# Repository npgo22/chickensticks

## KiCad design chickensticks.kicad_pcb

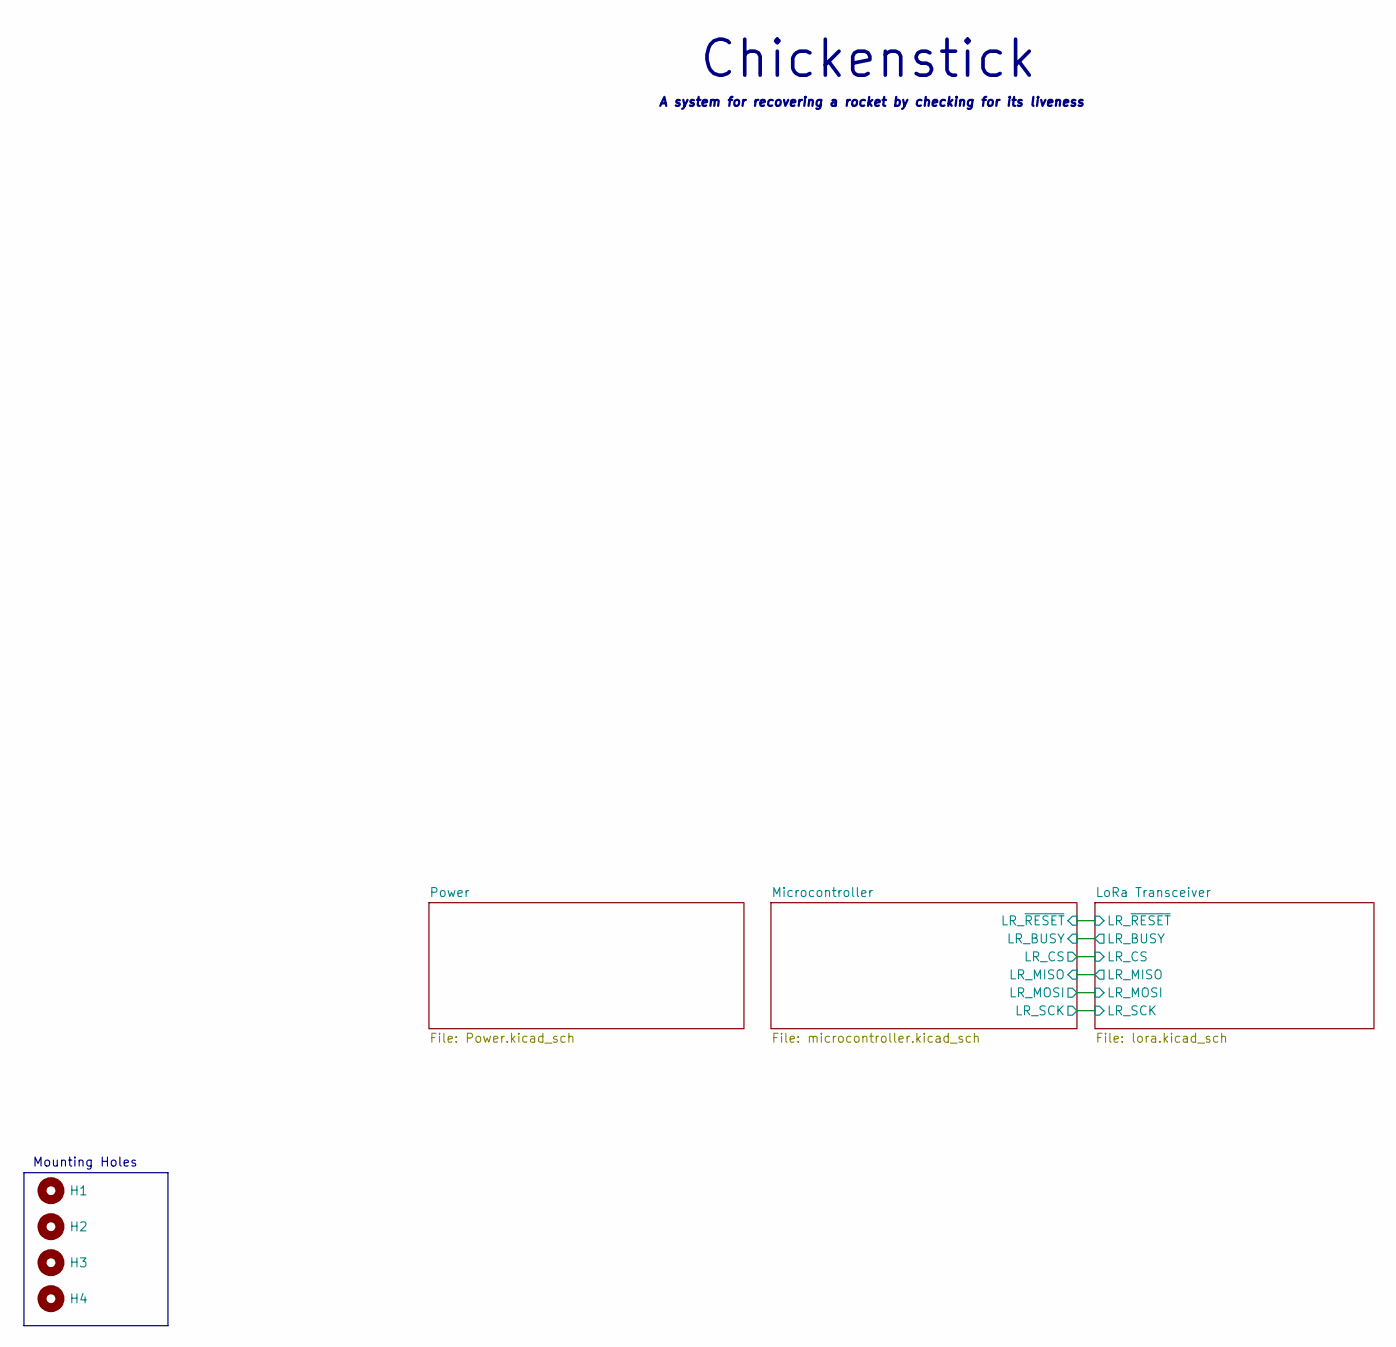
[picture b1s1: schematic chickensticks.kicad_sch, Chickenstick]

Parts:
H1, H2, H3, H4: MountingHole; MountingHole_3.2mm_M3

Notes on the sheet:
Chickenstick
A system for recovering a rocket by checking for its liveness
Mounting Holes

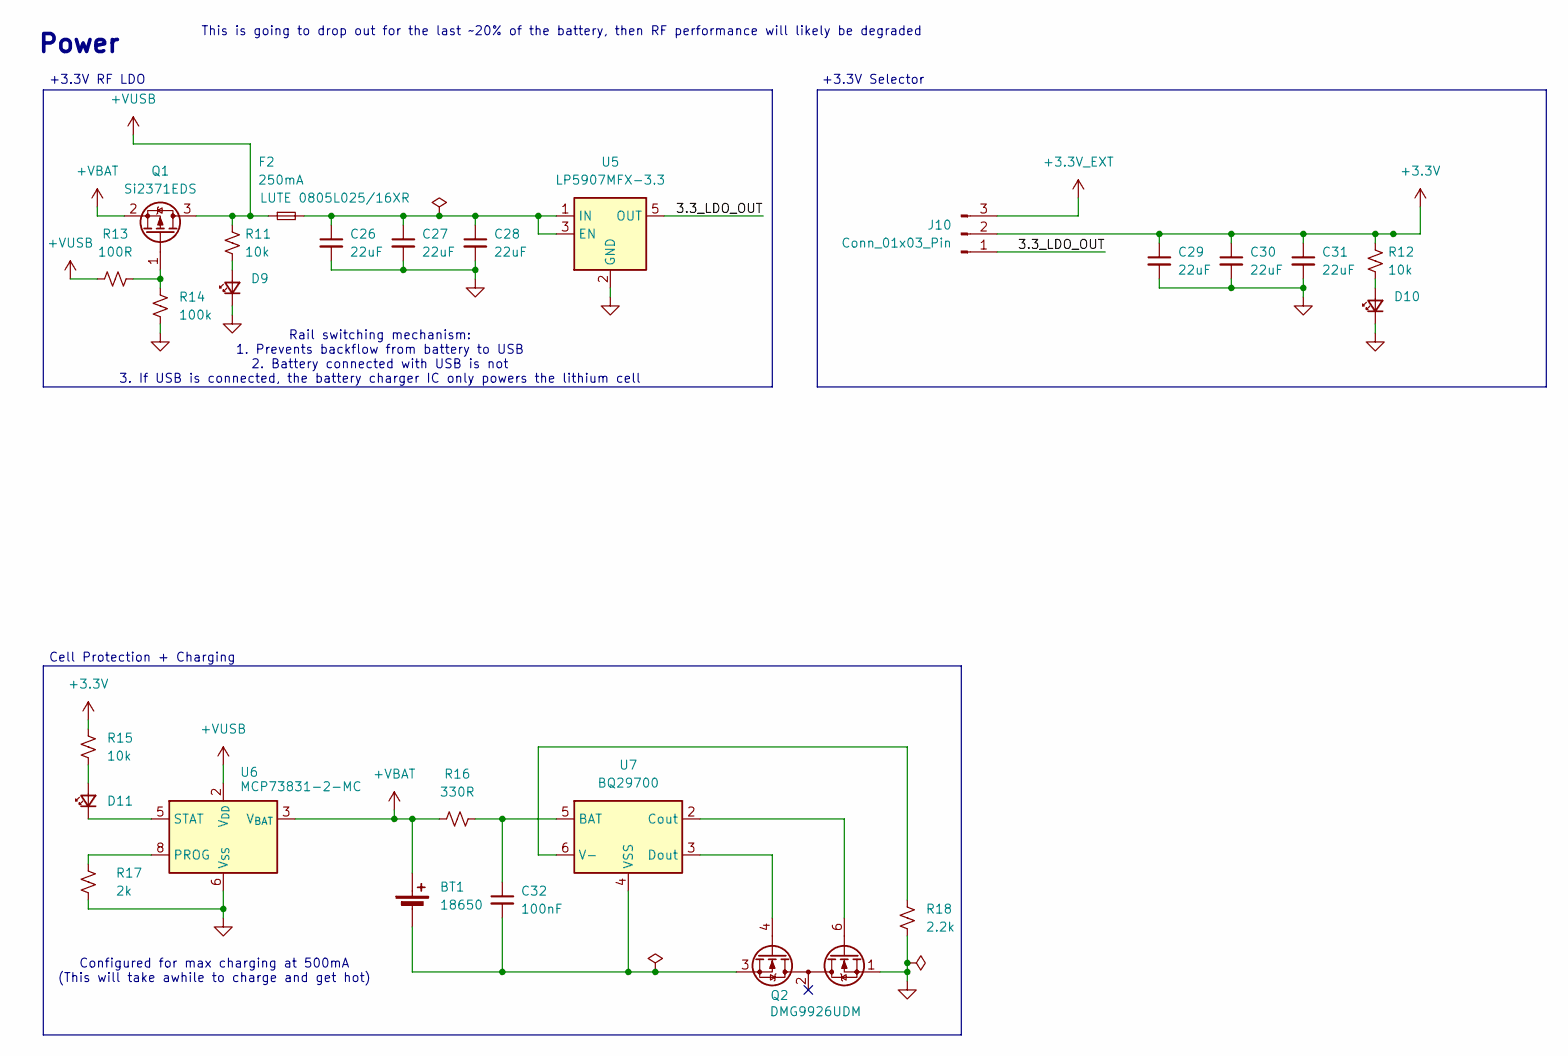
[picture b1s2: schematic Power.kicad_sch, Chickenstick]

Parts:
BT1: 18650; BatteryHolder_Keystone_1042_1x18650
C26, C27, C28, C29, C30, C31: 22uF; C_0805
C32: 100nF; C_0603
D9, D10, D11: LED_Small; LED_0603
F2: 250mA; Fuse_0805_2012Metric
J10: Conn_01x03_Pin; PinHeader_1x03_P2.54mm_Vertical
Q1: Si2371EDS; SOT-23
Q2: DMG9926UDM; SOT-23-6
R11, R12, R15: 10k; R_0603
R13: 100R; R_0603
R14: 100k; R_0603
R16: 330R; R_0603
R17: 2k; R_0603
R18: 2.2k; R_0603
U5: LP5907MFX-3.3; SOT-23-5
U6: MCP73831-2-MC; DFN-8-1EP_3x2mm_P0.5mm_EP1.7x1.4mm
U7: BQ29700; WSON-6_1.5x1.5mm_P0.5mm

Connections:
+3.3V: C29.1, C30.1, C31.1, J10.2, R12.1, R15.2; also elsewhere on the board
+3.3V_EXT: J10.3; also elsewhere on the board
+VUSB: F2.1, Q1.3 (D), R11.1, R13.1, U6.1 (V_{DD}), U6.2 (V_{DD}); also elsewhere on the board
/Power/3.3_LDO_OUT: J10.1, U5.5 (OUT)
unnamed: BT1.2 (-), C32.2, Q2.3 (S2), U7.4 (VSS)
unnamed: D9.2 (A), R11.2
unnamed: D10.2 (A), R12.2
unnamed: D11.2 (A), R15.1
unnamed: D11.1 (K), U6.5 (STAT)
unnamed: Q1.1 (G), R13.2, R14.1
unnamed: Q2.6 (G1), U7.2 (Cout)
unnamed: Q2.4 (G2), U7.3 (Dout)
unnamed: C26.1, C27.1, C28.1, F2.2, U5.1 (IN), U5.3 (EN)
unnamed: R17.1, U6.8 (PROG)
unnamed: C32.1, R16.2, U7.5 (BAT)
unnamed: R18.1, U7.6 (V-)

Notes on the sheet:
Configured for max charging at 500mA (This will take awhile to charge and get hot)
This is going to drop out for the last ~20% of the battery, then RF performance will likely be degraded
Power
Rail switching mechanism: 1. Prevents backflow from battery to USB 2. Battery connected with USB is not 3. If USB is connected, the battery charger IC only powers the lithium cell
+3.3V RF LDO
Cell Protection + Charging
+3.3V Selector

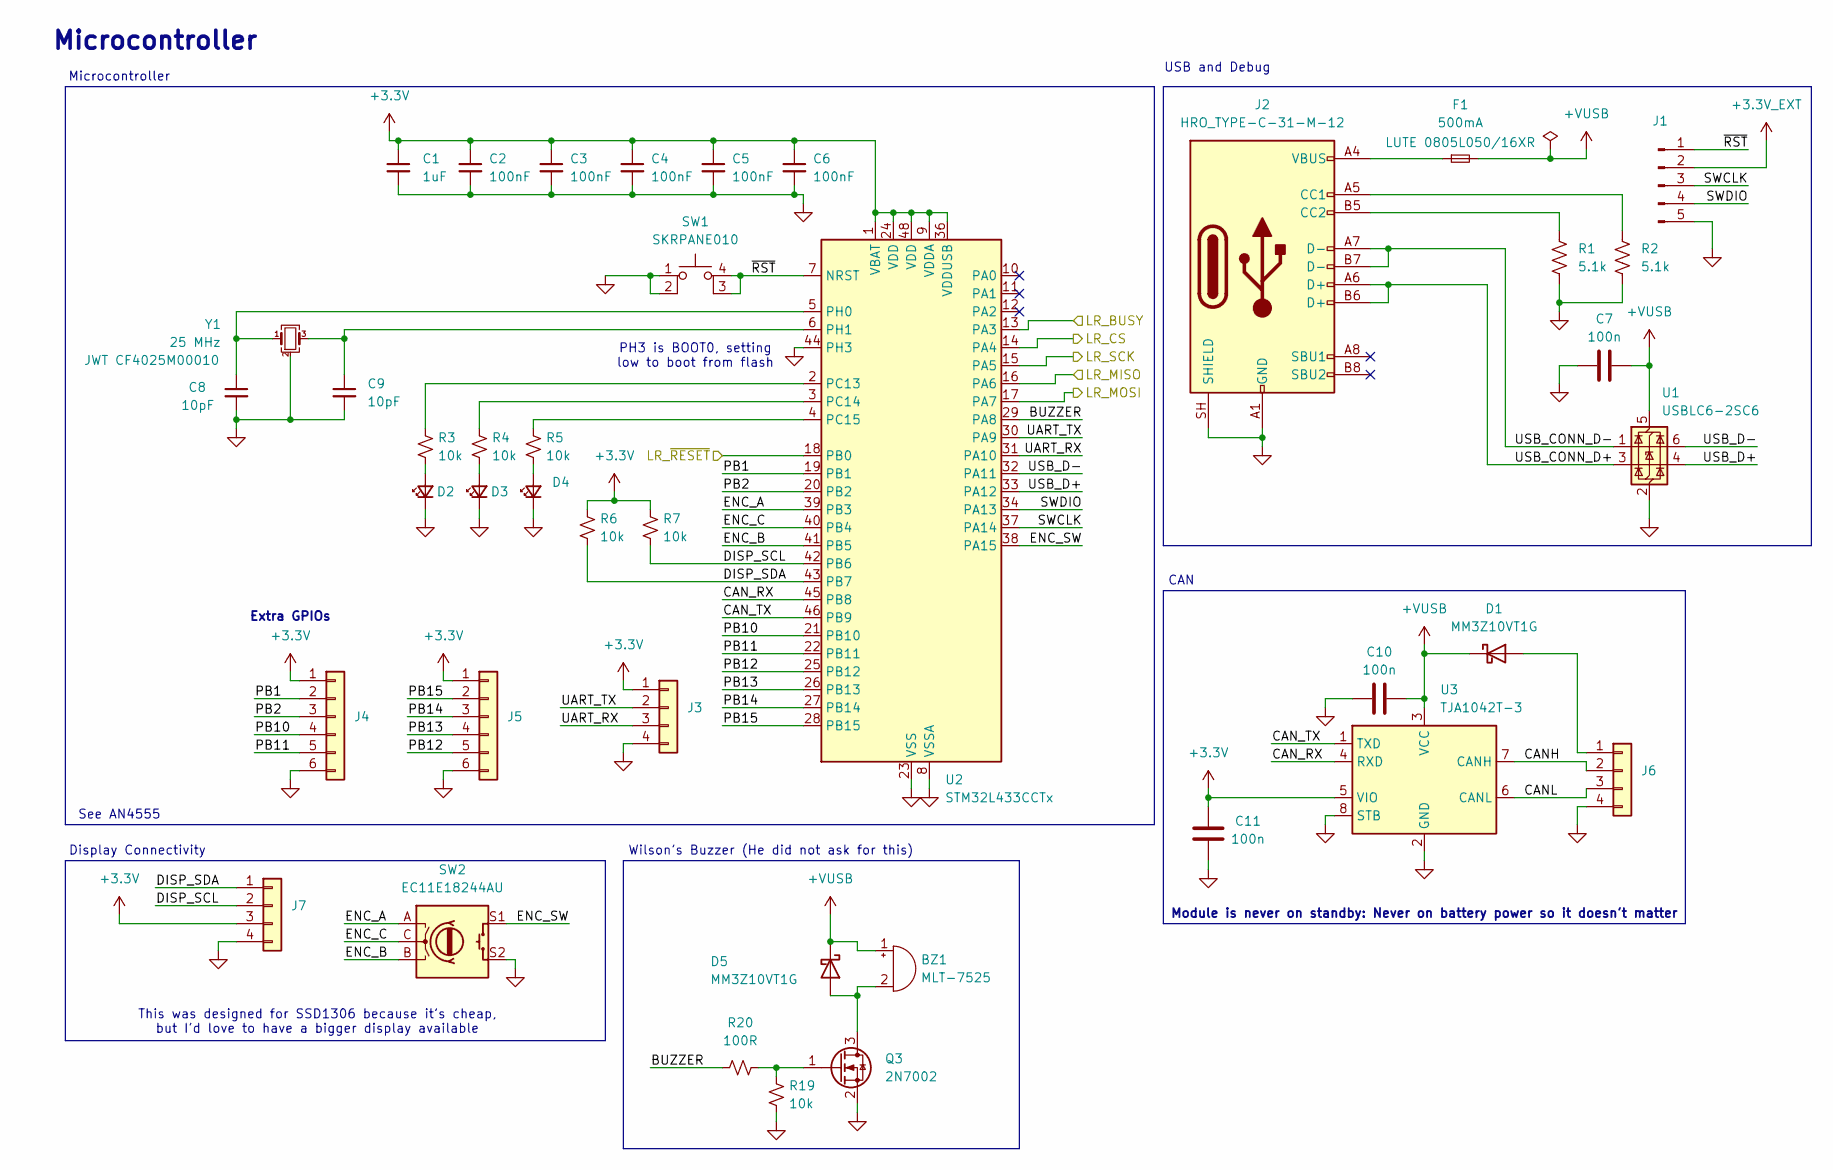
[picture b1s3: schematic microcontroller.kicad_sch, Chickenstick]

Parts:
BZ1: MLT-7525
C1: 1uF; C_0805
C2, C3, C4, C5, C6: 100nF; C_0603
C7, C10, C11: 100n; C_0603
C8, C9: 10pF; C_0603
D1, D5: MM3Z10VT1G; SOD-323
D2, D3, D4: LED_Small; LED_0603
F1: 500mA; Fuse_0805_2012Metric
J1: Conn_01x05_Pin; PinHeader_1x05_P2.54mm_Vertical
J2: HRO_TYPE-C-31-M-12; USB_C_Receptacle_HRO_TYPE-C-31-M-12
J3, J6, J7: Conn_01x04; PinHeader_1x04_P2.54mm_Vertical
J4, J5: Conn_01x06; PinHeader_1x06_P2.54mm_Vertical
Q3: 2N7002; SOT-23
R1, R2: 5.1k; R_0603
R3, R4, R5, R6, R7, R19: 10k; R_0603
R20: 100R; R_0603
SW1: SKRPANE010
SW2: EC11E18244AU; RotaryEncoder_Alps_EC11E-Switch_Vertical_H20mm_MountingHoles
U1: USBLC6-2SC6; SOT-23-6
U2: STM32L433CCTx; LQFP-48_7x7mm_P0.5mm
U3: TJA1042T-3; SOIC-8_3.9x4.9mm_P1.27mm
Y1: 25 MHz; 3225-4P-L

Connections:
+3.3V: C1.1, C2.1, C3.1, C4.1, C5.1, C6.1, C11.2, J3.1, J4.1, J5.1, J7.3, R6.1, R7.1, U2.1 (VBAT), U2.9 (VDDA), U2.24 (VDD), U2.36 (VDDUSB), U2.48 (VDD), U3.5 (VIO); also elsewhere on the board
+3.3V_EXT: J1.2; also elsewhere on the board
+VUSB: BZ1.1 (+), C7.2, C10.2, D1.1 (K), D5.1 (K), F1.2, U1.5 (VBUS), U3.3 (VCC); also elsewhere on the board
/LoRa Transceiver/LR_BUSY: U2.13 (PA3); also elsewhere on the board
/LoRa Transceiver/LR_CS: U2.14 (PA4); also elsewhere on the board
/LoRa Transceiver/LR_MISO: U2.16 (PA6); also elsewhere on the board
/LoRa Transceiver/LR_MOSI: U2.17 (PA7); also elsewhere on the board
/LoRa Transceiver/LR_SCK: U2.15 (PA5); also elsewhere on the board
/LoRa Transceiver/LR_~RESET: U2.18 (PB0); also elsewhere on the board
/Microcontroller/BUZZER: R20.1, U2.29 (PA8)
/Microcontroller/CANH: J6.2, U3.7 (CANH)
/Microcontroller/CANL: J6.3, U3.6 (CANL)
/Microcontroller/CAN_RX: U2.45 (PB8), U3.4 (RXD)
/Microcontroller/CAN_TX: U2.46 (PB9), U3.1 (TXD)
/Microcontroller/DISP_SCL: J7.2, R7.2, U2.42 (PB6)
/Microcontroller/DISP_SDA: J7.1, R6.2, U2.43 (PB7)
/Microcontroller/ENC_A: SW2.A, U2.39 (PB3)
/Microcontroller/ENC_B: SW2.B, U2.41 (PB5)
/Microcontroller/ENC_C: SW2.C, U2.40 (PB4)
/Microcontroller/ENC_SW: SW2.S1, U2.38 (PA15)
/Microcontroller/PB1: J4.2, U2.19 (PB1)
/Microcontroller/PB2: J4.3, U2.20 (PB2)
/Microcontroller/PB10: J4.4, U2.21 (PB10)
/Microcontroller/PB11: J4.5, U2.22 (PB11)
/Microcontroller/PB12: J5.5, U2.25 (PB12)
/Microcontroller/PB13: J5.4, U2.26 (PB13)
/Microcontroller/PB14: J5.3, U2.27 (PB14)
/Microcontroller/PB15: J5.2, U2.28 (PB15)
/Microcontroller/SWCLK: J1.3, U2.37 (PA14)
/Microcontroller/SWDIO: J1.4, U2.34 (PA13)
/Microcontroller/UART_RX: J3.3, U2.31 (PA10)
/Microcontroller/UART_TX: J3.2, U2.30 (PA9)
/Microcontroller/USB_CONN_D+: J2.A6 (D+), J2.B6 (D+), U1.3 (I/O2)
/Microcontroller/USB_CONN_D-: J2.A7 (D-), J2.B7 (D-), U1.1 (I/O1)
/Microcontroller/USB_D+: U1.4 (I/O2), U2.33 (PA12)
/Microcontroller/USB_D-: U1.6 (I/O1), U2.32 (PA11)
/Microcontroller/~RST: J1.1, SW1.3 (K), SW1.4 (A), U2.7 (NRST)
unnamed: BZ1.2 (-), D5.2 (A), Q3.3 (D)
unnamed: D1.2 (A), J6.1
unnamed: D2.2 (A), R3.2
unnamed: D3.2 (A), R4.2
unnamed: D4.2 (A), R5.2
unnamed: F1.1, J2.A4 (VBUS), J2.A9 (VBUS), J2.B4 (VBUS), J2.B9 (VBUS)
unnamed: J2.A5 (CC1), R2.1
unnamed: J2.B5 (CC2), R1.1
unnamed: Q3.1 (G), R19.1, R20.2
unnamed: R3.1, U2.2 (PC13)
unnamed: R4.1, U2.3 (PC14)
unnamed: R5.1, U2.4 (PC15)
unnamed: C8.1, U2.5 (PH0), Y1.1
unnamed: C9.1, U2.6 (PH1), Y1.3

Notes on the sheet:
Microcontroller
Extra GPIOs
Module is never on standby: Never on battery power so it doesn't matter
See AN4555
Display Connectivity
Wilson's Buzzer (He did not ask for this)
This was designed for SSD1306 because it's cheap, but I'd love to have a bigger display available
CAN
PH3 is BOOT0, setting low to boot from flash
USB and Debug

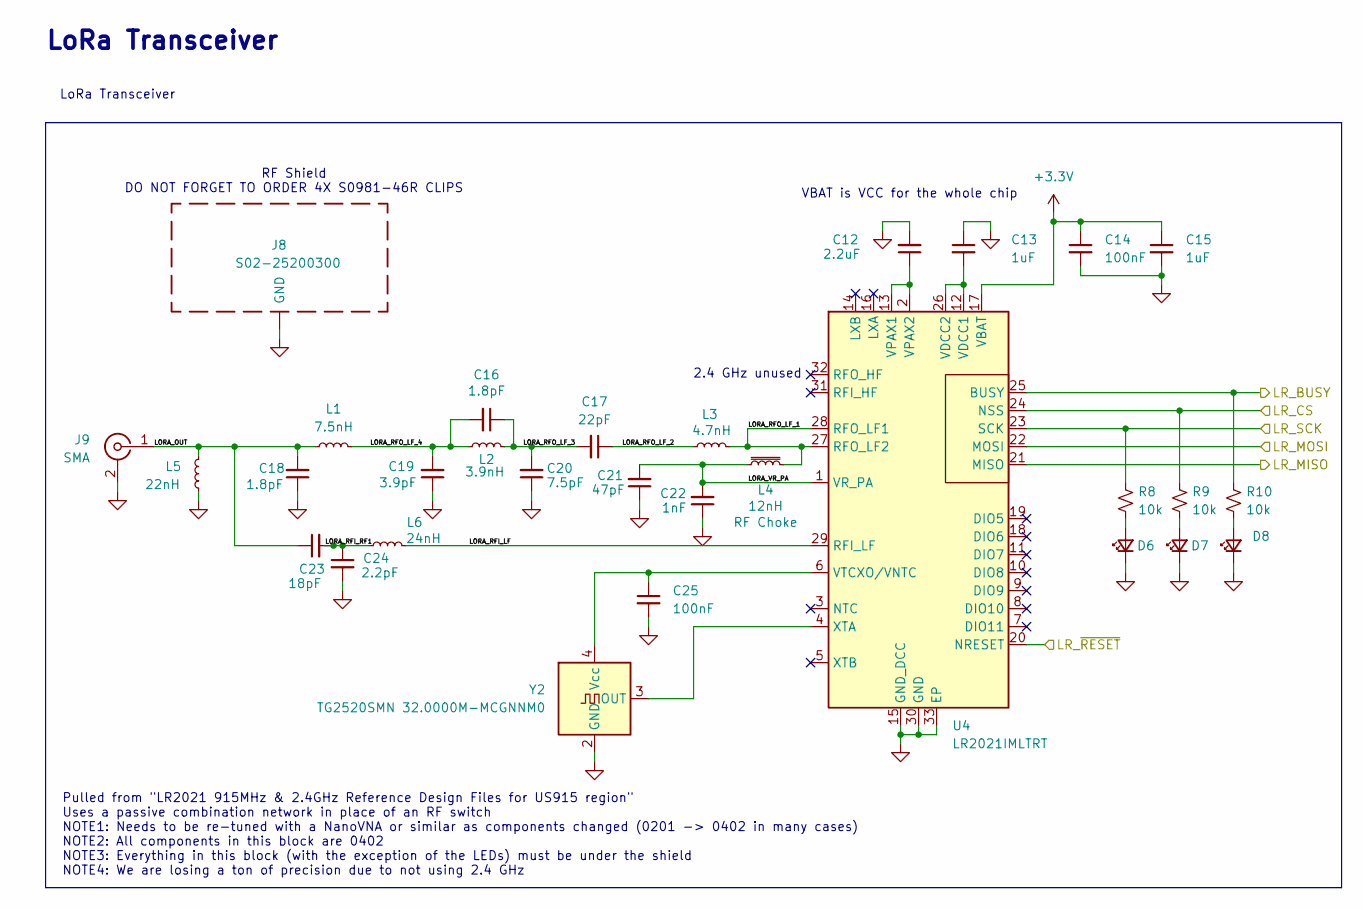
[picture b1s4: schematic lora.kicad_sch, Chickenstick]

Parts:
C12: 2.2uF; C_0805
C13, C15: 1uF; C_0805
C14, C25: 100nF; C_0603
C16, C18: 1.8pF; C_0402
C17: 22pF; C_0402
C19: 3.9pF; C_0402
C20: 7.5pF; C_0402
C21: 47pF; C_0402
C22: 1nF; C_0402
C23: 18pF; C_0402
C24: 2.2pF; C_0402
D6, D7, D8: LED_Small; LED_0603
J8: S02-25200300; S02-25200300-Outline
J9: SMA; SMA_Amphenol_132203-12_Horizontal
L1: 7.5nH; L_0402
L2: 3.9nH; L_0402
L3: 4.7nH; L_0402
L4: 12nH; L_0402
L5: 22nH; L_0402
L6: 24nH; L_0402
R8, R9, R10: 10k; R_0603
U4: LR2021IMLTRT; QFN-32_EP_5.8x5.8_Pitch0.5mm
Y2: TG2520SMN 32.0000M-MCGNNM0; Oscillator_SMD_SeikoEpson_TG2520SMN-xxx-xxxxxx-4Pin_2.5x2.0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

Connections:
+3.3V: C14.1, C15.1, U4.17 (VBAT); also elsewhere on the board
/LoRa Transceiver/LORA_OUT: C18.2, C23.1, J9.1 (In), L1.1, L5.2
/LoRa Transceiver/LORA_RFI_LF: L6.2, U4.29 (RFI_LF)
/LoRa Transceiver/LORA_RFI_RF1: C23.2, C24.1, L6.1
/LoRa Transceiver/LORA_RFO_LF_1: L3.2, L4.2, U4.27 (RFO_LF2), U4.28 (RFO_LF1)
/LoRa Transceiver/LORA_RFO_LF_2: C17.1, L3.1
/LoRa Transceiver/LORA_RFO_LF_3: C16.1, C17.2, C20.2, L2.2
/LoRa Transceiver/LORA_RFO_LF_4: C16.2, C19.2, L1.2, L2.1
/LoRa Transceiver/LORA_VR_PA: C21.2, C22.2, L4.1, U4.1 (VR_PA)
/LoRa Transceiver/LR_BUSY: R10.1, U4.25 (BUSY); also elsewhere on the board
/LoRa Transceiver/LR_CS: R9.1, U4.24 (NSS); also elsewhere on the board
/LoRa Transceiver/LR_MISO: U4.21 (MISO); also elsewhere on the board
/LoRa Transceiver/LR_MOSI: U4.22 (MOSI); also elsewhere on the board
/LoRa Transceiver/LR_SCK: R8.1, U4.23 (SCK); also elsewhere on the board
/LoRa Transceiver/LR_~RESET: U4.20 (NRESET); also elsewhere on the board
unnamed: D6.2 (A), R8.2
unnamed: D7.2 (A), R9.2
unnamed: D8.2 (A), R10.2
unnamed: C13.2, U4.12 (VDCC1), U4.26 (VDCC2)
unnamed: C12.1, U4.2 (VPAX2), U4.13 (VPAX1)
unnamed: C25.1, U4.6 (VTCXO/VNTC), Y2.4 (Vcc)
unnamed: U4.4 (XTA), Y2.3 (OUT)

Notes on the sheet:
RF Shield DO NOT FORGET TO ORDER 4X S0981-46R CLIPS
2.4 GHz unused
Pulled from "LR2021 915MHz & 2.4GHz Reference Design Files for US915 region" Uses a passive combination network in place of an RF switch NOTE1: Needs to be re-tuned with a NanoVNA or similar as components changed (0201 -> 0402 in many cases) NOTE2: All components in this block are 0402 NOTE3: Every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
VBAT is VCC for the whole chip
LoRa Transceiver

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
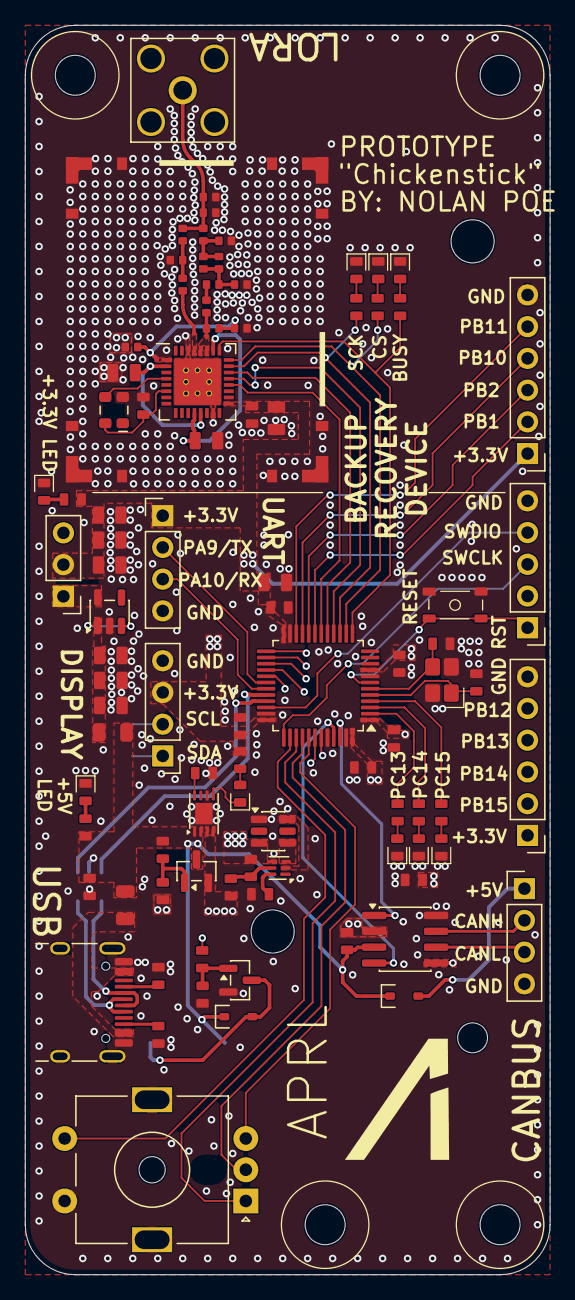
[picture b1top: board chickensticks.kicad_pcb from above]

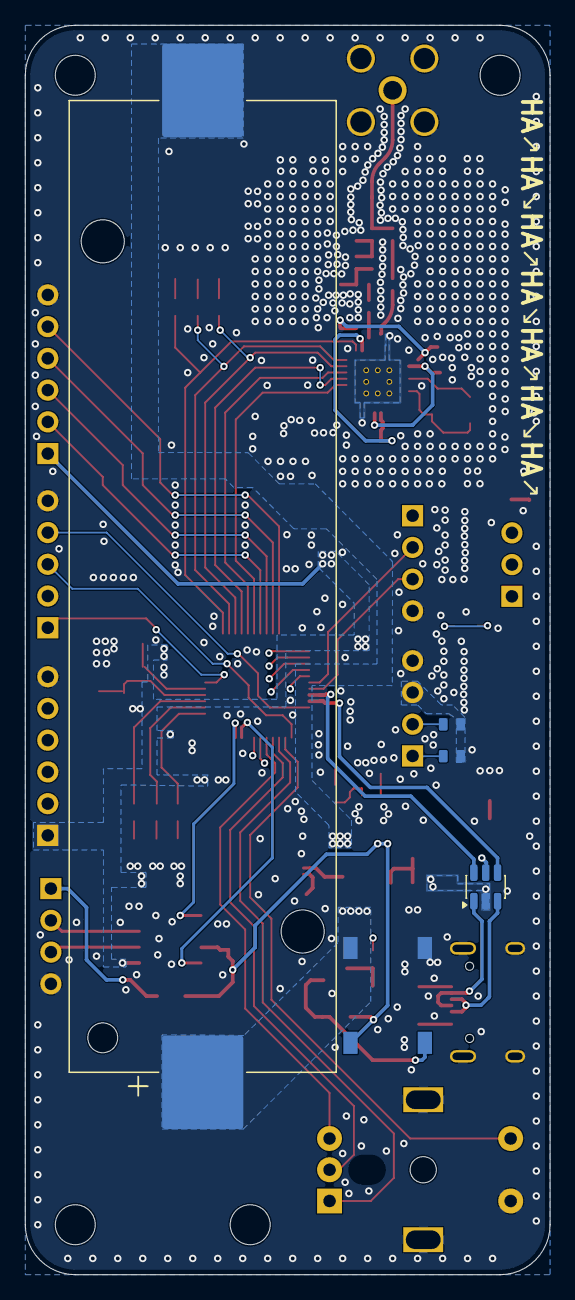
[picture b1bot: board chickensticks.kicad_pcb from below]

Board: 4 copper layers, 42.0 x 100.0 mm, 101 parts (5 on the bottom side), 81 nets.

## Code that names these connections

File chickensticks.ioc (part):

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Mcu.Name=STM32L433C(B-C)Tx
Mcu.Package=LQFP48
Mcu.UserName=STM32L433CCTx
PA10.Mode=Asynchronous
PA10.Signal=USART1_RX
PA11.Mode=Device
PA11.Signal=USB_DM
PA12.Mode=Device
PA12.Signal=USB_DP
PA13\ (JTMS-SWDIO).Mode=Serial_Wire
PA13\ (JTMS-SWDIO).Signal=SYS_JTMS-SWDIO
PA14\ (JTCK-SWCLK).Mode=Serial_Wire
PA14\ (JTCK-SWCLK).Signal=SYS_JTCK-SWCLK
PA15\ (JTDI).Signal=GPIO_Input
PA3.GPIOParameters=GPIO_Label
PA3.GPIO_Label=LR_BUSY
PA3.Signal=GPIO_Input
PA4.GPIOParameters=GPIO_Label
PA4.GPIO_Label=LR_CS
PA4.Signal=GPIO_Output
PA5.Mode=Full_Duplex_Master
PA5.Signal=SPI1_SCK
PA6.Mode=Full_Duplex_Master
PA6.Signal=SPI1_MISO
PA7.Mode=Full_Duplex_Master
PA7.Signal=SPI1_MOSI
PA9.Mode=Asynchronous
PA9.Signal=USART1_TX
PB0.GPIOParameters=GPIO_Label
PB0.GPIO_Label=LR_RESET
PB0.Signal=GPIO_Output
PB3\ (JTDO-TRACESWO).Signal=GPIO_Input
PB4\ (NJTRST).Signal=GPIO_Input
PB5.Signal=GPIO_Input
PB6.Mode=I2C
PB6.Signal=I2C1_SCL
PB7.Mode=I2C
PB7.Signal=I2C1_SDA
PB8.Mode=CAN_Activate
PB8.Signal=CAN1_RX
PB9.Mode=CAN_Activate
PB9.Signal=CAN1_TX
PC13.GPIOParameters=GPIO_Label
PC13.GPIO_Label=LED1
PC13.Signal=GPIO_Output
PC14-OSC32_IN\ (PC14).GPIOParameters=GPIO_Label
PC14-OSC32_IN\ (PC14).GPIO_Label=LED2
PC14-OSC32_IN\ (PC14).Signal=GPIO_Output
PC15-OSC32_OUT\ (PC15).GPIOParameters=GPIO_Label
PC15-OSC32_OUT\ (PC15).GPIO_Label=LED3
PC15-OSC32_OUT\ (PC15).Signal=GPIO_Output
PH0-OSC_IN\ (PH0).Mode=HSE-External-Oscillator
PH0-OSC_IN\ (PH0).Signal=RCC_OSC_IN
PH1-OSC_OUT\ (PH1).Mode=HSE-External-Oscillator
PH1-OSC_OUT\ (PH1).Signal=RCC_OSC_OUT
PH3-BOOT0.GPIOParameters=GPIO_Label
PH3-BOOT0.GPIO_Label=BOOT0
PH3-BOOT0.Signal=EVENTOUT
RCC.HSE_VALUE=25000000
RCC.SYSCLKFreq_VALUE=80000000
RCC.SYSCLKSource=RCC_SYSCLKSOURCE_PLLCLK
board=custom

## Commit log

2026-04-24 Initial review version
2026-04-24 Implement first stage of review fixes
2026-04-24 Add buzzer, fix some erc
2026-04-24 Try kibot dev_k10 image
2026-04-24 Run cleanup tracks and vias
2026-04-28 Remove big SS14 diodes
2026-04-28 Add external 3.3V selector (noise is not real anyway)
2026-06-29 Add renovate.json
